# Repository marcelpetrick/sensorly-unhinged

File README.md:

<div align="center">

# sensorly-unhinged

### A tiny sensor. Two very different ways to build it.

**My very first PCB project — an open hardware experiment in measuring the cost of compactness.**

[Explore the two designs](#meet-the-contenders) · [See what is verified](#status) · [Build it yourself](#build) · [Follow the plan](plan.md)

</div>

A battery-powered indoor temperature and humidity node sounds simple. Put the
sensor next to a radio, charger and battery, though, and the board can become
part of what it measures.

This project asks a practical question: **is a larger, thermally isolated design
worth its extra space, cost and mechanical complexity?** Instead of choosing by
intuition, it develops one electrical platform in two physical forms, with a
predeclared experiment to decide between them.

**Author:** [Marcel Petrick](mailto:mail@marcelpetrick.it) · **License:** [GPL-3.0-or-later](LICENSE)

**AI disclosure:** this project is generated with AI. Its design claims still need
traceable sources, review and physical verification.

## Meet the contenders

| **A — Compact · HW A1** | **B — Thermally isolated · HW B1** |
|:---:|:---:|
|  |  |
| **30 × 34 mm** PCB | **30 × 51 mm** PCB envelope |
| One rectangle; sensor at the edge | Sensor island on a **3.5 × 8 mm** FR-4 neck |
|  |  |
| **47.0 × 39.2 × 19.6 mm** enclosure | **47.0 × 56.2 × 19.6 mm** enclosure |
| One chamber | Two chambers, divided at the neck |

*These are generated previews, not photographs. Board renders omit component
bodies; enclosure fit and thermal benefit remain unmeasured.* Dimensions come
from the [floorplan](docs/40-floorplans.md) and
[enclosure model](docs/80-enclosure.md).

Both variants share the **ESP32-C6-MINI-1**, **SHT45-AD1F**, **BQ24074** charger,
**TPS62840** regulator, schematic, BOM and firmware. A protected 1S LiPo and
USB-C provide the power interfaces. Only geometry, thermal isolation and the
enclosure change.

The experiment is **5 A + 5 B**, compared with a reference instrument. The
[thermal test plan](docs/50-thermal-ab-test-plan.md) declares the decision gate
before the boards exist — including the conditions under which the simpler
compact design wins. B has to earn its extra space.

## What makes this worth following

- **The comparison stays fair.** One shared electrical model emits both boards;
  changes to values, nets and rules are considered together.
- **The case is part of the instrument.** Vents, chamber walls, battery placement
  and sensor supports belong in the thermal design.
- **Measure first, transmit later.** The firmware contract requires acquisition
  before the radio powers up; the current bring-up image keeps the radio off.
- **The work is inspectable.** Parametric KiCad generation, OpenSCAD models,
  datasheet references, fault-injection tests and release gates live alongside
  the design. Failed experiments remain in the execution history.

## Status

> **Engineering prototype — not ready for fabrication or use.**
> Source checks pass; complete routing, supplier reviews and real-hardware
> qualification are still required.

The current routing checkpoint (2026-11-13) is recorded in [the plan](plan.md):

| Check | Current evidence |
|---|---|
| Shared electrical design | One schematic, BOM and firmware for A and B |
| ERC / DRC / schematic parity | **0 violations, 0 errors, 0 warnings, 0 parity differences** |
| Routing | **A: 18 / B: 12 open connections**; zero GND/USB-data airwires |
| Reproducibility | Generated sources regenerate byte-identically |
| Local verification | Local checkpoint `9d3ba3a`: **15 stages**, 166 host tests and 41 actual KiCad controls pass; A18/B12 opens remain |
| Bring-up firmware | Pinned ESP-IDF build; radio disabled; acquired samples written to a reviewed flash journal |
| Physical qualification | Still open; no measured A/B advantage or qualified charging claim |

Exact routing counts live in [`hardware/drc-budget.json`](hardware/drc-budget.json).
The [execution record](docs/01-execution-plan.md) retains source revisions and
verification history. BLE provisioning, MQTT/TLS delivery, signed OTA and the
remaining product behavior are tracked in the
[firmware contract](docs/71-firmware-contract.md).

**Next:** finish routing → complete independent design and supplier reviews →
produce and inspect the controlled 5 + 5 lot → run the A/B experiment → revise
and qualify a controlled 20-unit series. The [flight manual](docs/02-flight-manual.md)
provides the procedures and stop conditions.

The [first engineering source prerelease](https://github.com/marcelpetrick/sensorly-unhinged/releases/tag/engineering-2026-10-22)
is available to explore. It is a source snapshot, not a manufacturing release.
The quality badge tracks `master`; the repository-owned release labels describe
that separate release state without an empty workflow or nonexistent-latest-release badge.

## Follow the circuit

One schematic feeds both layouts. Start with the
[electrical design specification](docs/30-electrical-design-spec.md) for values,
sources and open decisions, or open the
[KiCad source](hardware/schematic/env-sensor.kicad_sch).

## Build

Everything runs from `make`. The full local gate prints a PASS/FAIL summary:

```bash
./localPipeline.sh
```

For a first look without KiCad:

```bash
make check          # shared-model rules
make test           # host regression and fault-injection tests
make firmware-test  # C sensor-decoder and flash-journal tests
```

Python-only checks include `check`, `test`, `bom`, `thermal`, `cost` and `power`.
Firmware host tests require a C compiler and standard C development headers
(`gcc` and `libc6-dev` on the Debian CI image). ERC/DRC and exports require
**KiCad 10** (`kicad-cli`); enclosure meshes require **OpenSCAD**. The real
firmware build uses pinned **ESP-IDF v5.5.4** — follow the
[bring-up instructions](docs/72-firmware-bringup.md).

<details>
<summary><strong>Build commands and release gates</strong></summary>

```bash
make license        # SPDX headers on authored source
make gen            # shared schematic, both boards, rules and model SVGs
make erc drc        # shared schematic + filled-board checks and parity
make bom            # BOM and netlist from the shared model
make thermal cost   # geometry-based screening model and cost estimate
make mech           # enclosure checks, parameters and available STL outputs
make outputs        # DRAFT Gerbers, drill, CPL, assembly PDF and STEP
make render         # board PNG previews
make mech-render    # enclosure PNG previews; graphics display required
make power          # illustrative budget; replace assumptions with measurements
make firmware       # source the pinned ESP-IDF export.sh first
make prototype-check
make prototype-package PROTOTYPE_VARIANT=a
make release-check
make release-package RELEASE_TAG=hw-a1
```

The package commands are deliberately blocked while their required evidence or
complete routing is missing. Use the selected board's printed revision and
variant when packaging; `hw-a1` and `a` above are examples.

GitHub's **Hardware Quality** workflow runs `localPipeline.sh` and retains draft
outputs for 14 days. The manual **Hardware Release** workflow checks the printed
revision, complete routing, qualification evidence and source provenance before
packaging. Publication is opt-in and draft by default. A clean development DRC
or a successful `make outputs` does not authorize an order.

Read [release packaging](docs/64-release-packaging.md) and the
[prototype-to-production handoff](docs/65-prototype-to-production.md) before
preparing either kind of package.

</details>

## Find your way around

| If you want to… | Start here |
|---|---|
| See what is next | [Current plan](plan.md) · [Verified history](docs/01-execution-plan.md) |
| Understand the circuit | [Component choices](docs/20-component-selection.md) · [Electrical specification](docs/30-electrical-design-spec.md) |
| Inspect the physical trade-off | [Floorplans](docs/40-floorplans.md) · [Thermal screening model](docs/45-thermal-model.md) · [Enclosure](docs/80-enclosure.md) |
| Examine the experiment | [Predeclared A/B test plan](docs/50-thermal-ab-test-plan.md) |
| Check sourcing and cost | [Cost estimate](docs/60-manufacturing-cost.md) · [Cost reduction](docs/61-cost-reduction.md) · [Component audit](docs/96-component-audit-20261110.md) |
| Bring up a real sample | [Power qualification](docs/51-power-safety-qualification.md) · [Firmware and capture](docs/72-firmware-bringup.md) |
| Contribute or review | [Current implementation review](docs/99-current-state-review-20261112.md) · [Working agreement](AGENTS.md) · [Flight manual](docs/02-flight-manual.md) · [Requirements](docs/10-requirements.md) |
| Explore the longer journey | [14-phase roadmap](docs/00-plan.md) · [Original vision](docs/vision.md) |

```text
tools/boardgen/  shared electrical model, geometry, placement, routing and checks
hardware/       shared schematic, A/B layouts and verified libraries
mechanical/     OpenSCAD enclosures and generated parameters
firmware/       ESP-IDF bring-up application and host tests
production/     flashing, fixture capture and factory-test tooling
measurements/   protocols and raw-data structure for physical experiments
docs/           decisions, sources, reviews and operating procedures
```

## Licence

**GPL-3.0-or-later** — see [`LICENSE`](LICENSE). That covers everything authored
here: the generator, the schematic and both boards, the enclosure model, the
documents. Every authored source file carries an SPDX header, the generated
KiCad files carry it in their title block, and `make license` fails the build if
one is missing — a licence that only exists at the repository root stops
travelling the moment a file is copied out.

Two things in the tree are not ours and keep their own terms:

| | |
|---|---|
| `hardware/lib/sensorly.pretty/*` and `hardware/lib/sensorly.kicad_sym` (except the two authored parts) | from the [official KiCad libraries](https://gitlab.com/kicad/libraries), CC-BY-SA 4.0 **with the KiCad library exception** — which explicitly permits unlimited use in your own designs without imposing licence terms on the design itself. See `hardware/lib/README.md`. |
| Datasheet figures quoted in `docs/` | the manufacturers'. Cited, not reproduced. |

The KiCad library exception is what makes this combination clean: the footprints
can sit inside a GPL project without the CC-BY-SA terms propagating to the board.

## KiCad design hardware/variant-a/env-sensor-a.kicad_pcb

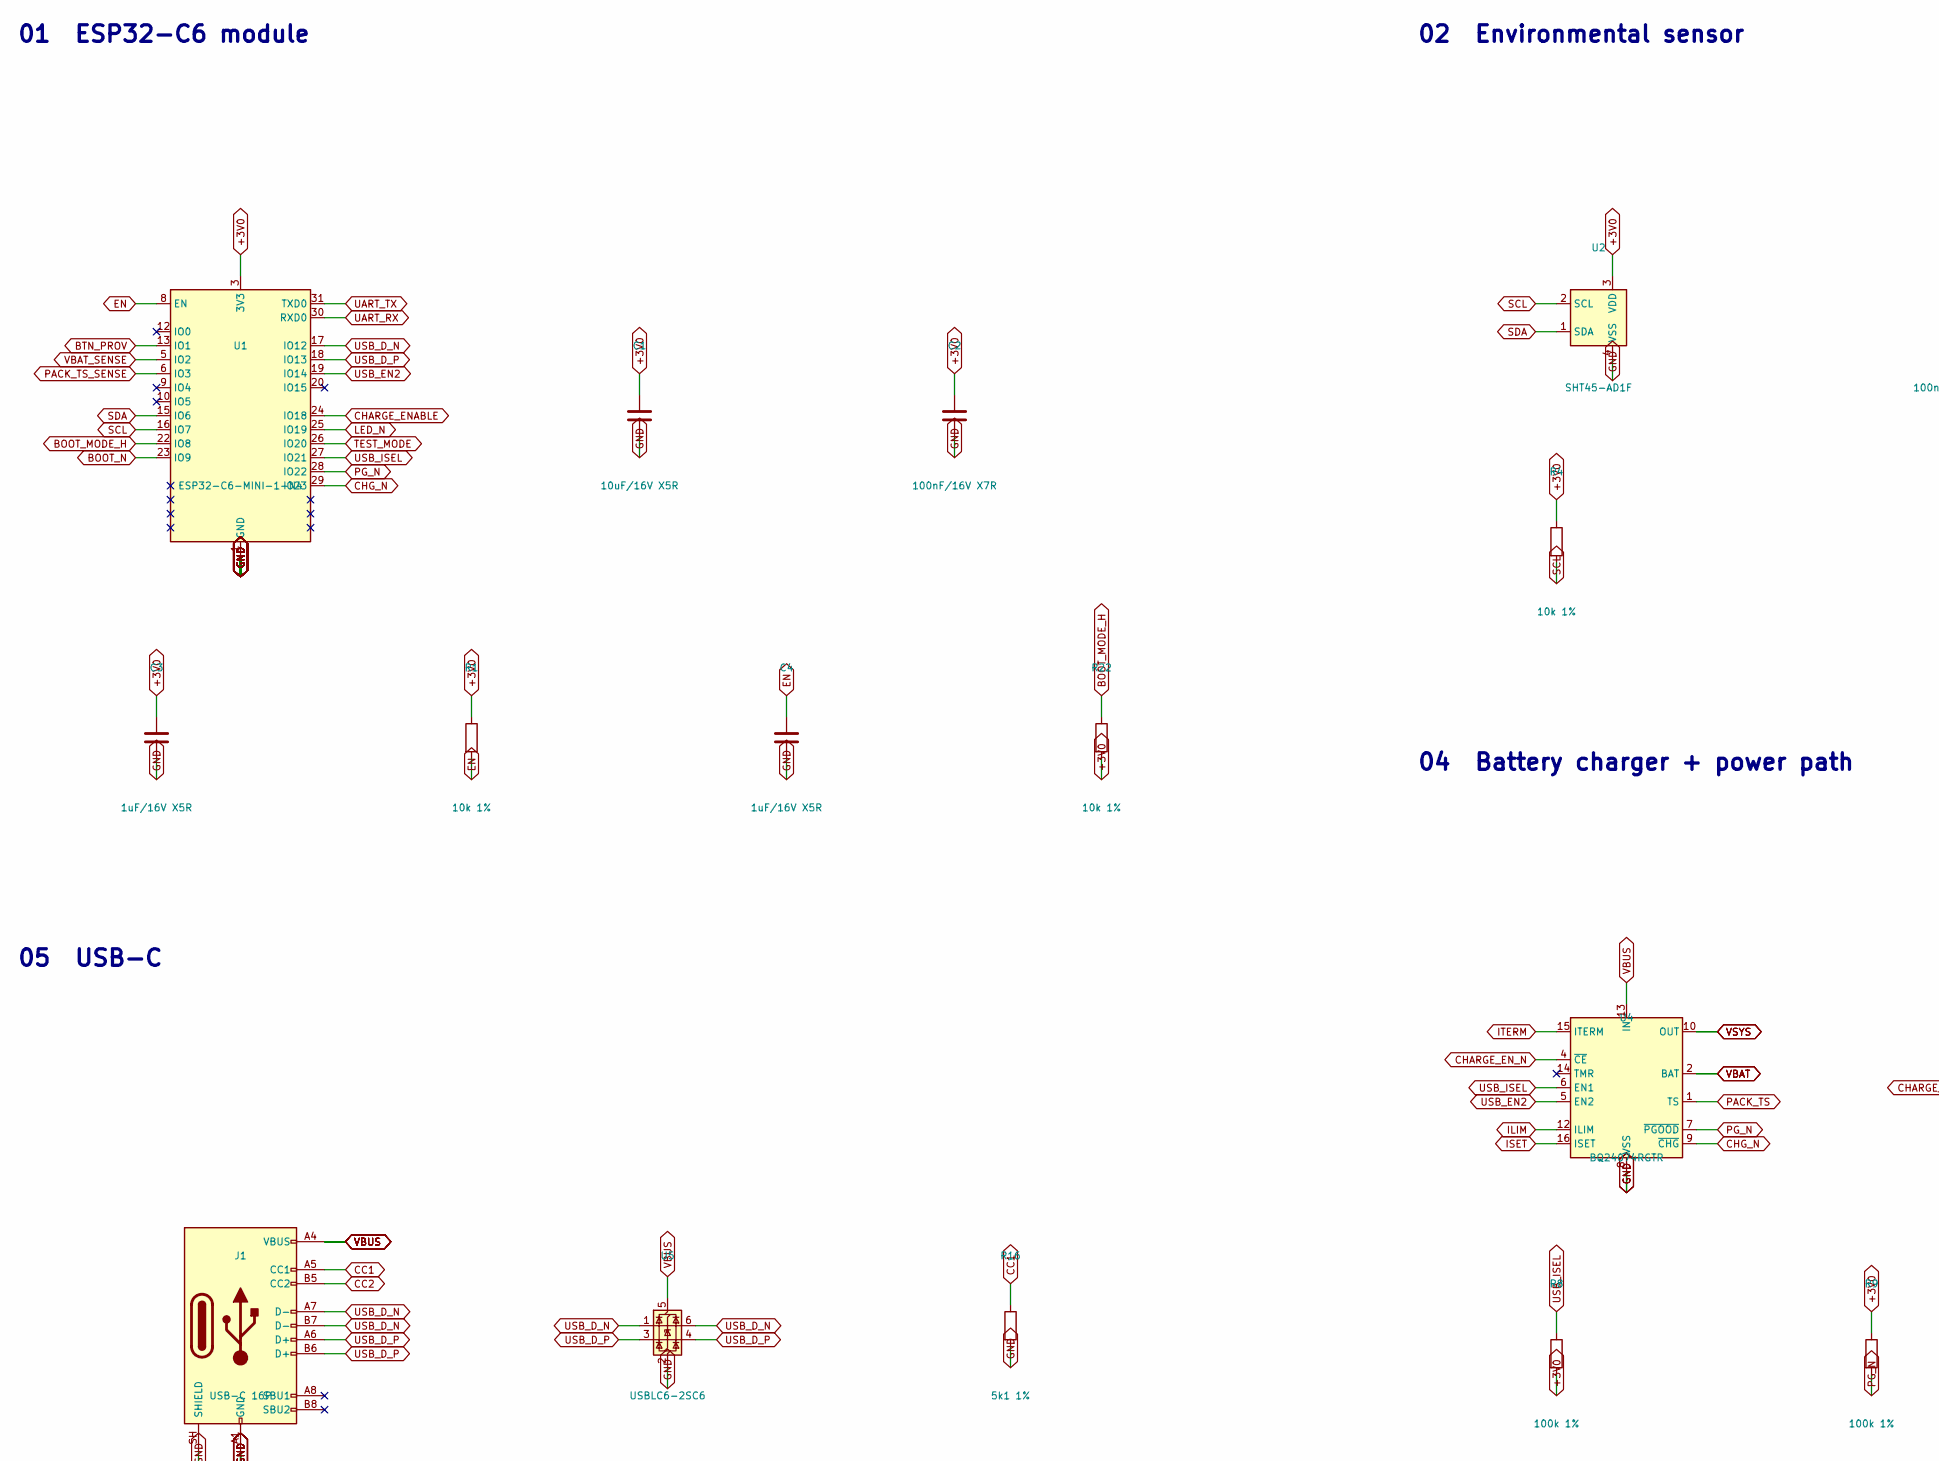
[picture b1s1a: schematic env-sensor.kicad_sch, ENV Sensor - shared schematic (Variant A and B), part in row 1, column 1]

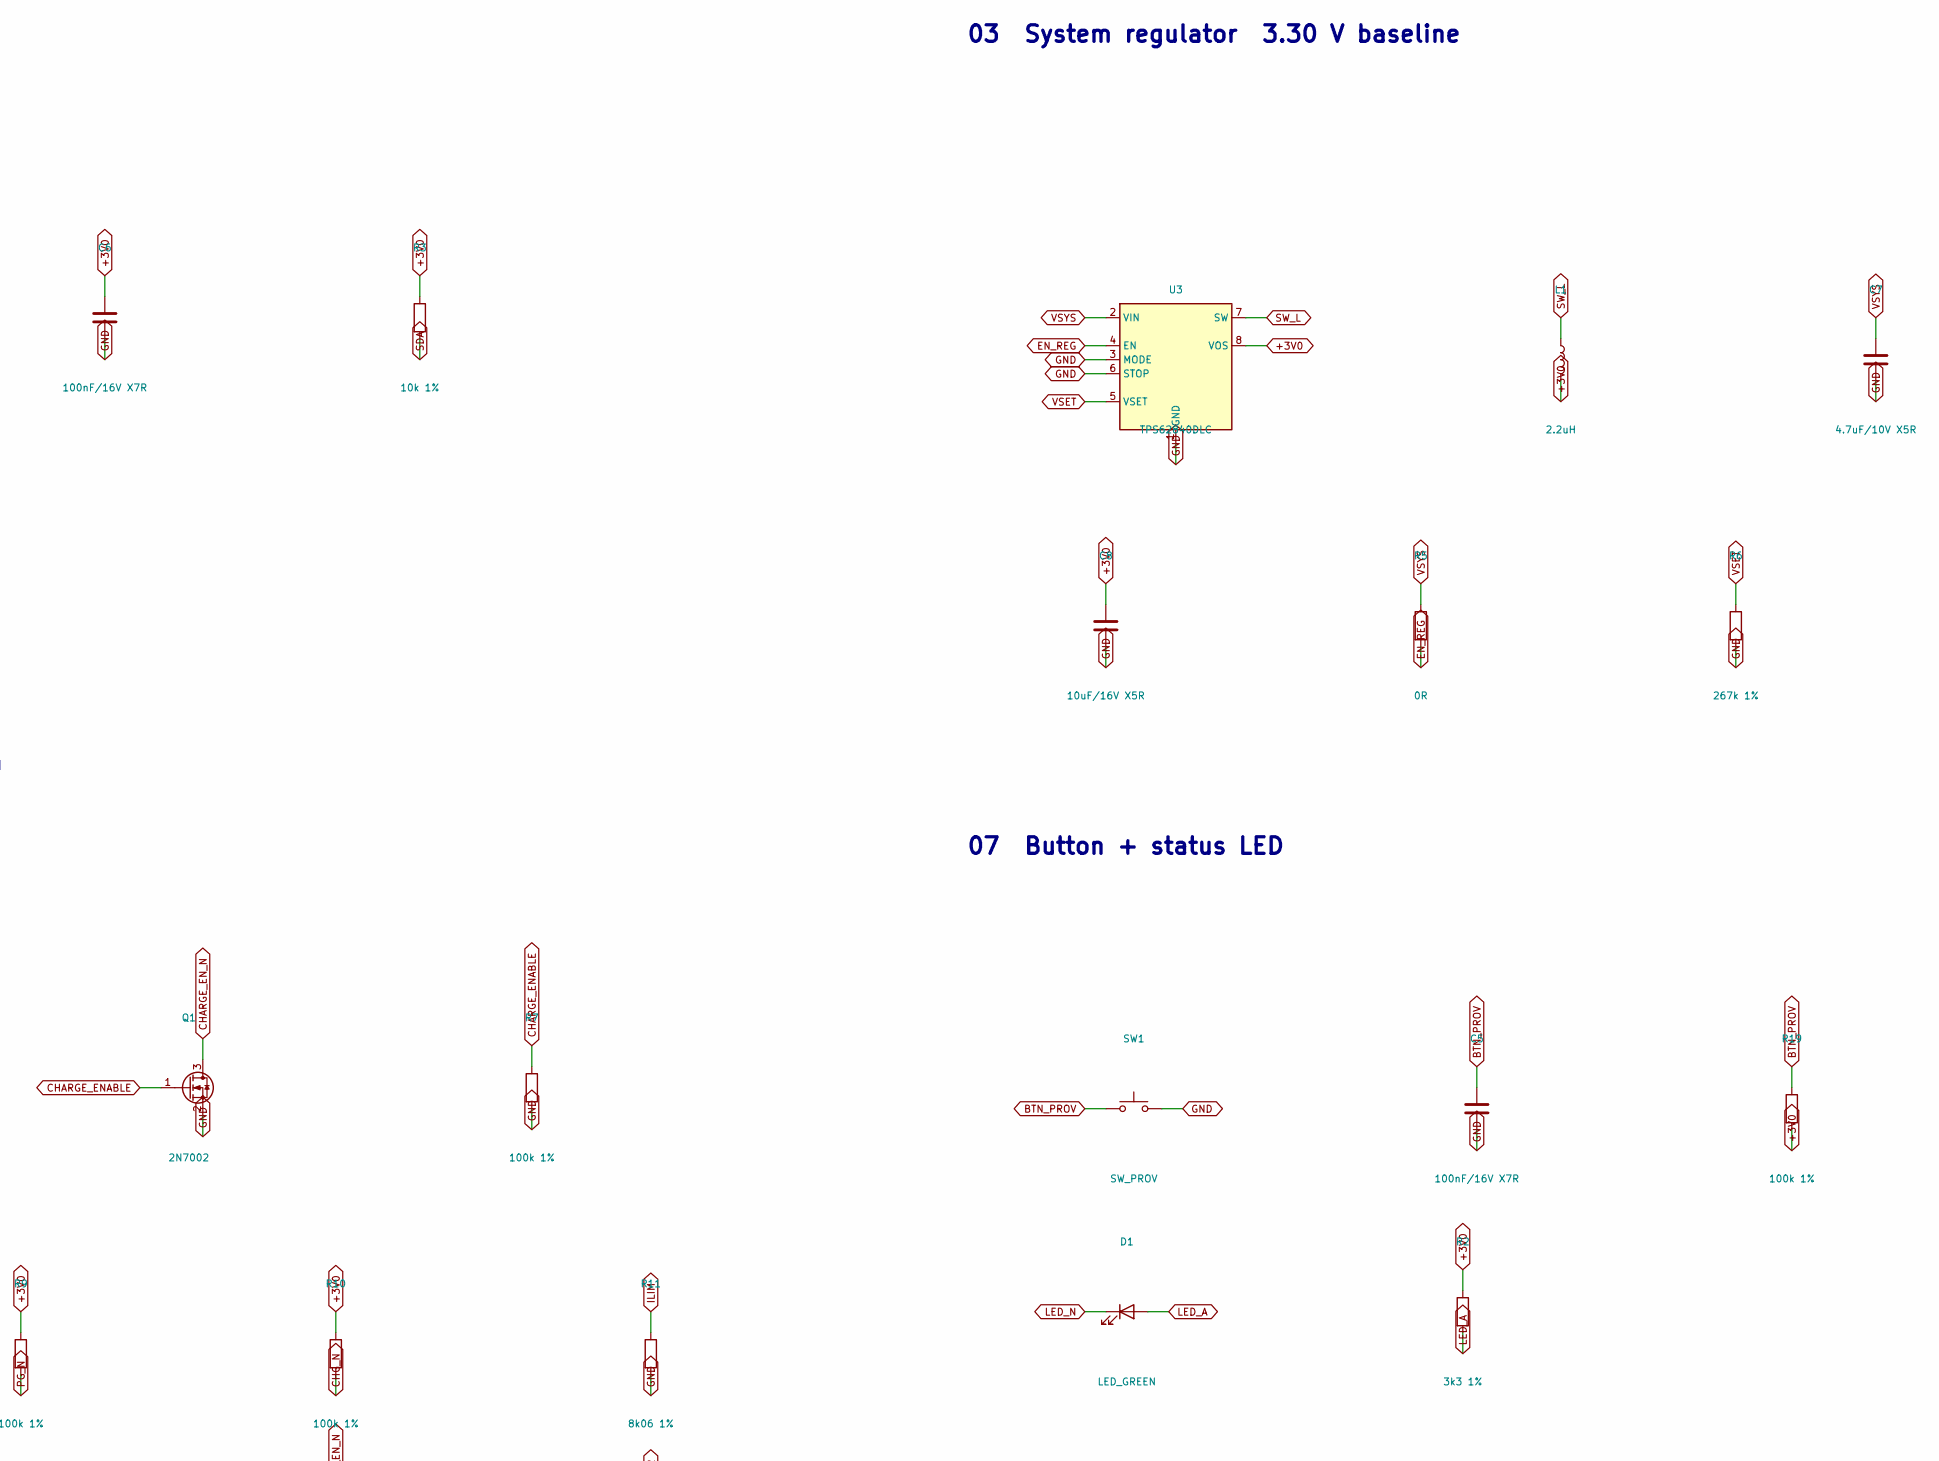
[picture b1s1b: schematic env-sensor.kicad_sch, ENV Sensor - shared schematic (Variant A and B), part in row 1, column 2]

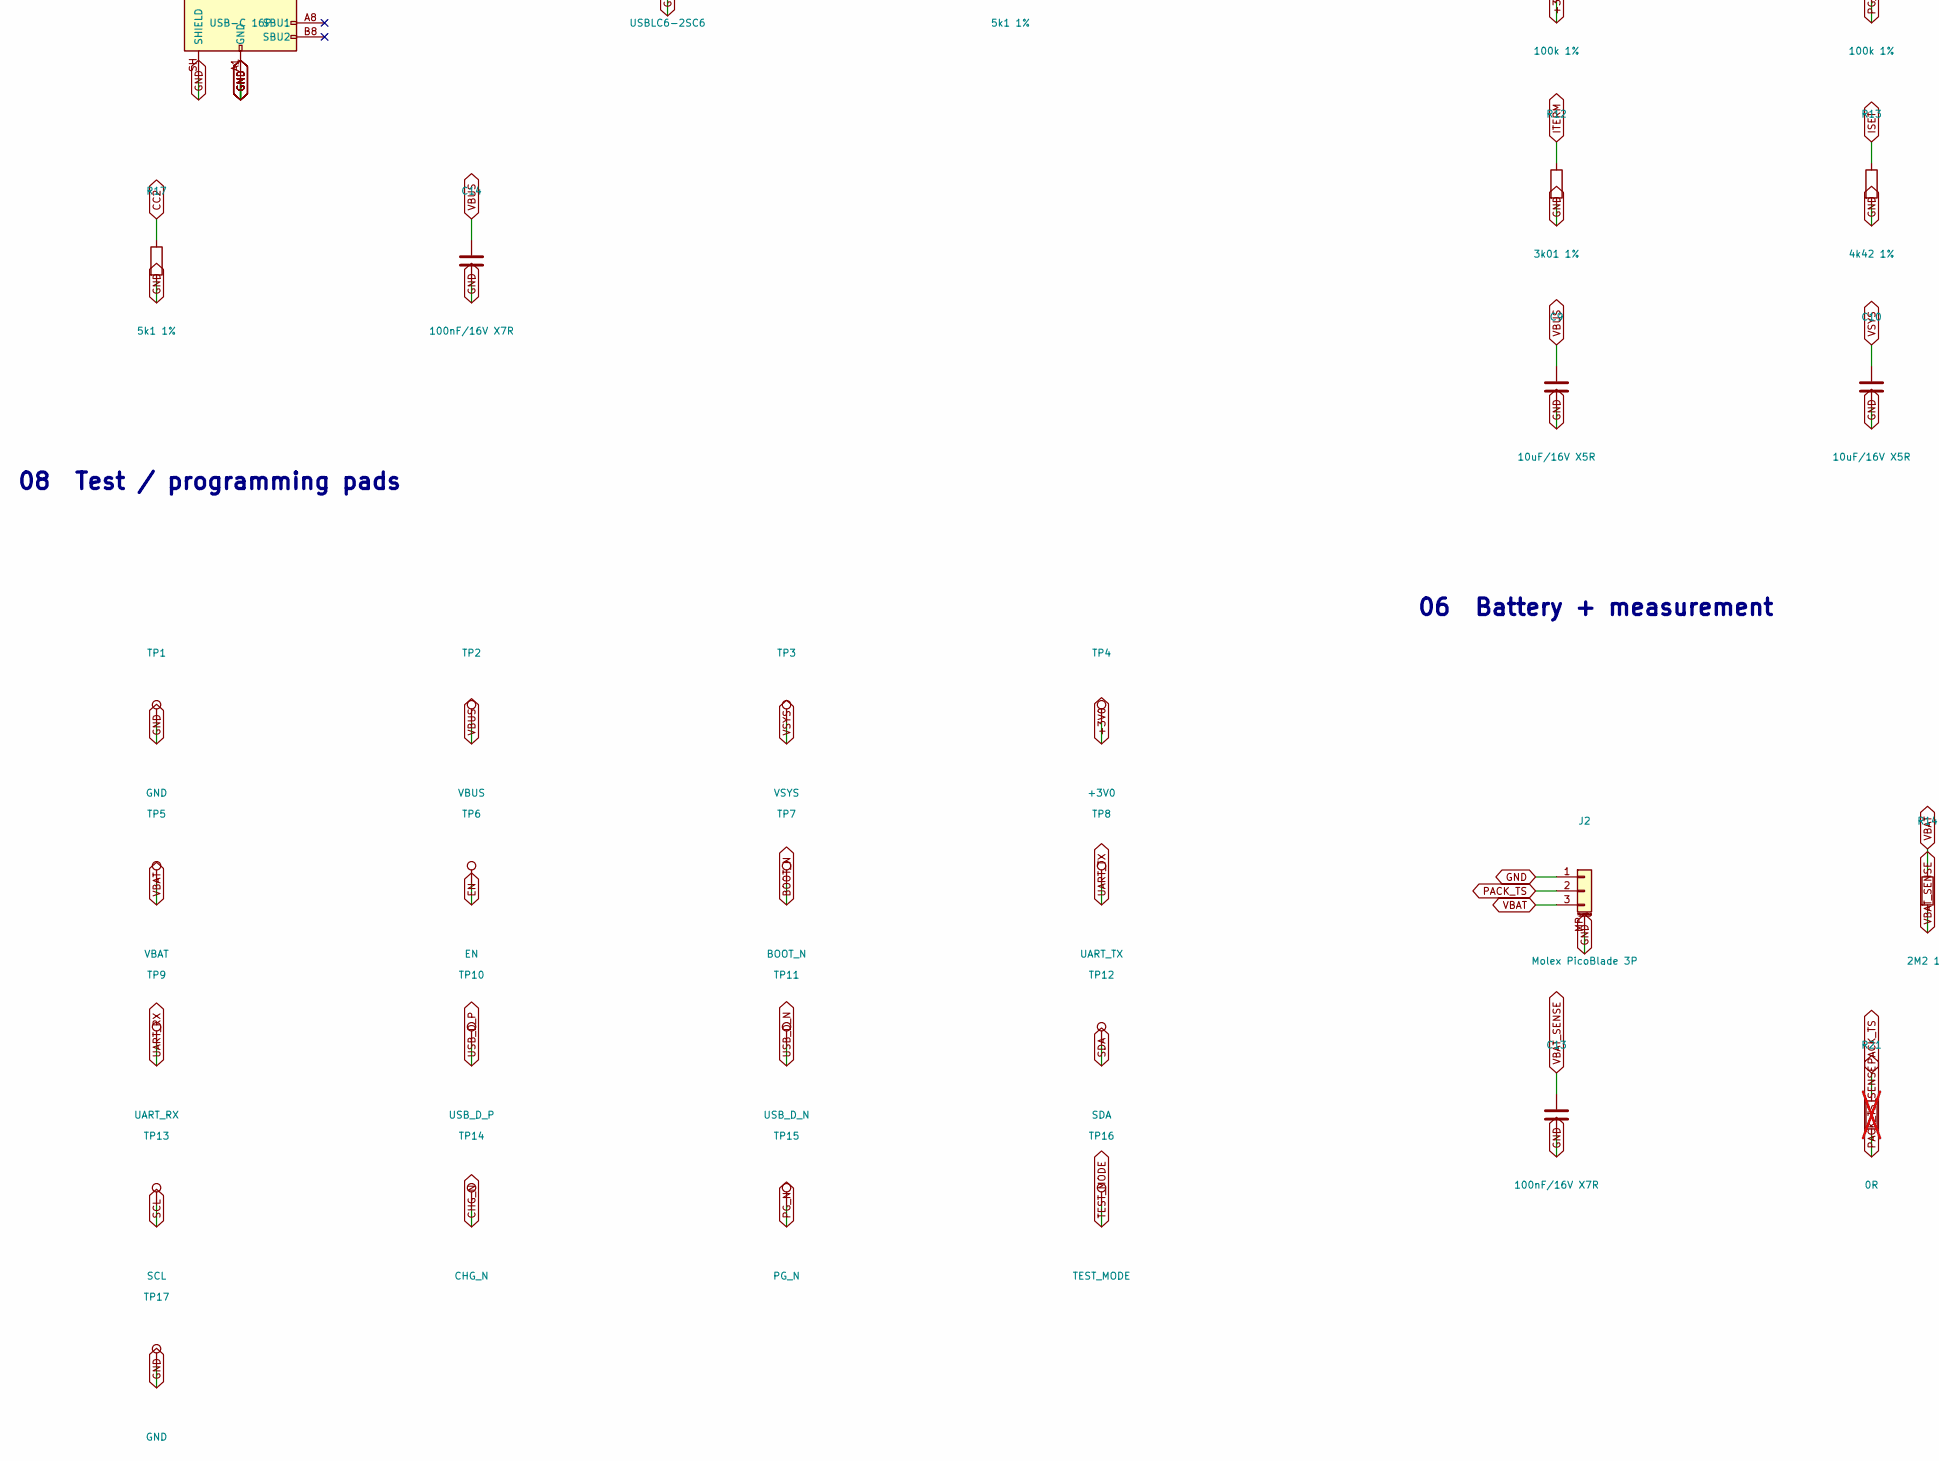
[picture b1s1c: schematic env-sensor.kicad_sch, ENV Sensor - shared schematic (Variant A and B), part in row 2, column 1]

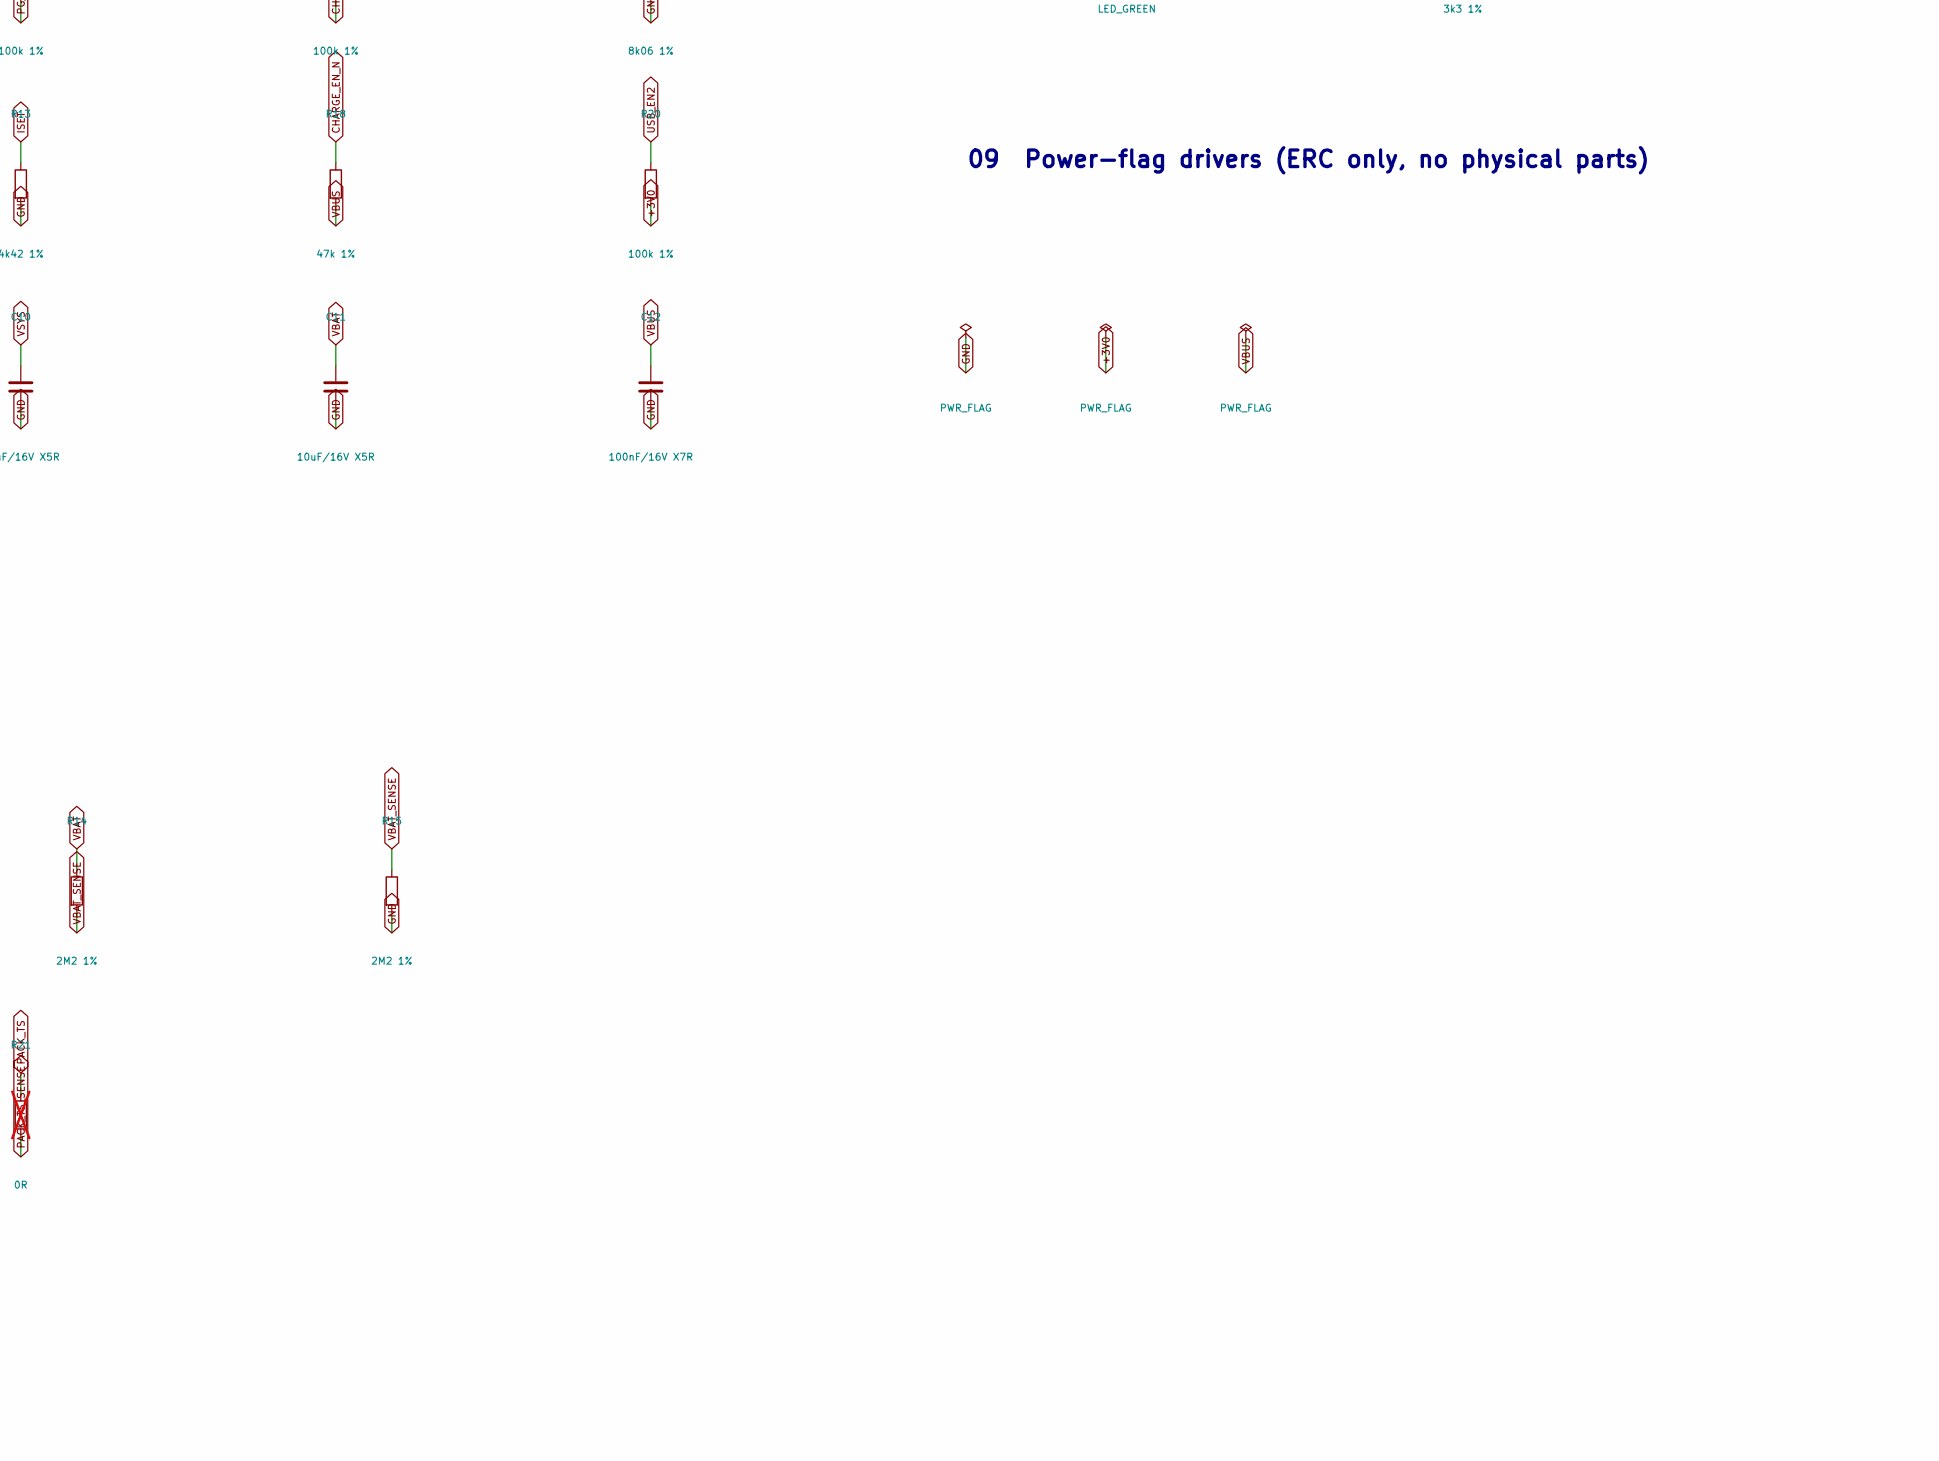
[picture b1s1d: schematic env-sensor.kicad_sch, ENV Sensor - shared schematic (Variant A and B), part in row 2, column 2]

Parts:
C1, C8, C9, C10, C11: 10uF/16V X5R; C_0805_2012Metric
C2, C5, C6, C12, C13, C14: 100nF/16V X7R; C_0402_1005Metric
C3, C4: 1uF/16V X5R; C_0402_1005Metric
C7: 4.7uF/10V X5R; C_0603_1608Metric
D1: LED_GREEN; Kingbright_KP1608SGC
J1: USB-C 16P; USB_C_Receptacle_HRO_TYPE-C-31-M-12
J2: Molex PicoBlade 3P; Molex_PicoBlade_53261-0371_1x03-1MP_P1.25mm_Horizontal
L1: 2.2uH; L_Murata_DFE201612E
Q1: 2N7002; Onsemi_CASE318_SOT23
R1, R3, R4, R22: 10k 1%; R_0402_1005Metric
R2: 3k3 1%; R_0402_1005Metric
R5: 0R; R_0402_1005Metric
R6: 267k 1%; R_0402_1005Metric
R7, R8, R9, R10, R19, R20: 100k 1%; R_0402_1005Metric
R11: 8k06 1%; R_0402_1005Metric
R12: 3k01 1%; R_0402_1005Metric
R13: 4k42 1%; R_0402_1005Metric
R14, R15: 2M2 1%; R_0402_1005Metric
R16, R17: 5k1 1%; R_0402_1005Metric
R18: 47k 1%; R_0402_1005Metric
R21: 0R; R_0402_1005Metric; not fitted
SW1: SW_PROV; Panasonic_EVQPUJ_EVQPUA
TP1, TP17: GND; TestPad_D1.5mm_Bottom
TP2: VBUS; TestPad_D1.5mm_Bottom
TP3: VSYS; TestPad_D1.5mm_Bottom
TP4: +3V0; TestPad_D1.5mm_Bottom
TP5: VBAT; TestPad_D1.5mm_Bottom
TP6: EN; TestPad_D1.5mm_Bottom
TP7: BOOT_N; TestPad_D1.5mm_Bottom
TP8: UART_TX; TestPad_D1.5mm_Bottom
TP9: UART_RX; TestPad_D1.5mm_Bottom
TP10: USB_D_P; TestPad_D1.5mm_Bottom
TP11: USB_D_N; TestPad_D1.5mm_Bottom
TP12: SDA; TestPad_D1.5mm_Bottom
TP13: SCL; TestPad_D1.5mm_Bottom
TP14: CHG_N; TestPad_D1.5mm_Bottom
TP15: PG_N; TestPad_D1.5mm_Bottom
TP16: TEST_MODE; TestPad_D1.5mm_Bottom
U1: ESP32-C6-MINI-1-N4; ESP32-C6-MINI-1
U2: SHT45-AD1F; Sensirion_DFN-4_1.5x1.5mm_P0.8mm_SHT4x_NoCentralPad
U3: TPS62840DLC; TI_DLC0008B_VSON-HR-8_2x1.5mm_P0.5mm
U4: BQ24074RGTR; TI_RGT0016B_VQFN16_3x3mm
U5: USBLC6-2SC6; ST_USBLC6_SOT23_6

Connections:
+3V0: C1.1, C2.1, C3.1, C6.1, C8.1, L1.2, R1.1, R2.1, R3.1, R4.1, R8.2, R9.1, R10.1, R19.2, R20.2, R22.2, TP4.1, U1.3 (3V3), U2.3 (VDD), U3.8 (VOS)
BOOT_MODE_H: R22.1, U1.22 (IO8)
BOOT_N: TP7.1, U1.23 (IO9)
BTN_PROV: C5.1, R19.1, SW1.1, U1.13 (IO1)
CC1: J1.A5 (CC1), R16.1
CC2: J1.B5 (CC2), R17.1
CHARGE_ENABLE: Q1.1 (G), R7.1, U1.24 (IO18)
CHARGE_EN_N: Q1.3 (D), R18.1, U4.4 (~CE)
CHG_N: R10.2, TP14.1, U1.29 (IO23), U4.9 (~CHG)
EN: C4.1, R1.2, TP6.1, U1.8 (EN)
EN_REG: R5.2, U3.4 (EN)
GND: C1.2, C2.2, C3.2, C4.2, C5.2, C6.2, C7.2, C8.2, C9.2, C10.2, C11.2, C12.2, C13.2, C14.2, J1.A1 (GND), J1.A12 (GND), J1.B1 (GND), J1.B12 (GND), J1.SH (SHIELD), J2.1, J2.MP (MountPin), Q1.2 (S), R6.2, R7.2, R11.2, R12.2, R13.2, R15.2, R16.2, R17.2, SW1.2, TP1.1, TP17.1, U1.1 (GND), U1.2 (GND), U1.11 (GND), U1.14 (GND), U1.36 (GND), U1.37 (GND), U1.38 (GND), U1.39 (GND), U1.40 (GND), U1.41 (GND), U1.42 (GND), U1.43 (GND), U1.44 (GND), U1.45 (GND), U1.46 (GND), U1.47 (GND), U1.48 (GND), U1.49 (GND), U1.50 (GND), U1.51 (GND), U1.52 (GND), U1.53 (GND), U2.4 (VSS), U3.1 (GND), U3.3 (MODE), U3.6 (STOP), U4.8 (VSS), U4.17 (VSS), U5.2 (GND)
ILIM: R11.1, U4.12 (ILIM)
ISET: R13.1, U4.16 (ISET)
ITERM: R12.1, U4.15 (ITERM)
LED_A: D1.1 (A), R2.2
LED_N: D1.2 (K), U1.25 (IO19)
PACK_TS: J2.2, R21.1, U4.1 (TS)
PACK_TS_SENSE: R21.2, U1.6 (IO3)
PG_N: R9.2, TP15.1, U1.28 (IO22), U4.7 (~PGOOD)
SCL: R4.2, TP13.1, U1.16 (IO7), U2.2 (SCL)
SDA: R3.2, TP12.1, U1.15 (IO6), U2.1 (SDA)
SW_L: L1.1, U3.7 (SW)
TEST_MODE: TP16.1, U1.26 (IO20)
UART_RX: TP9.1, U1.30 (RXD0)
UART_TX: TP8.1, U1.31 (TXD0)
USB_D_N: J1.A7 (D-), J1.B7 (D-), TP11.1, U1.17 (IO12), U5.1 (I/O1), U5.6 (I/O1)
USB_D_P: J1.A6 (D+), J1.B6 (D+), TP10.1, U1.18 (IO13), U5.3 (I/O2), U5.4 (I/O2)
USB_EN2: R20.1, U1.19 (IO14), U4.5 (EN2)
USB_ISEL: R8.1, U1.27 (IO21), U4.6 (EN1)
VBAT: C11.1, J2.3, R14.1, TP5.1, U4.2 (BAT), U4.3 (BAT)
VBAT_SENSE: C13.1, R14.2, R15.1, U1.5 (IO2)
VBUS: C9.1, C12.1, C14.1, J1.A4 (VBUS), J1.A9 (VBUS), J1.B4 (VBUS), J1.B9 (VBUS), R18.2, TP2.1, U4.13 (IN), U5.5 (VBUS)
VSET: R6.1, U3.5 (VSET)
VSYS: C7.1, C10.1, R5.1, TP3.1, U3.2 (VIN), U4.10 (OUT), U4.11 (OUT)

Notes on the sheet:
01 ESP32-C6 module
05 USB-C
08 Test / programming pads
02 Environmental sensor
04 Battery charger + power path
06 Battery + measurement
03 System regulator 3.30 V baseline
07 Button + status LED
09 Power-flag drivers (ERC only, no physical parts)

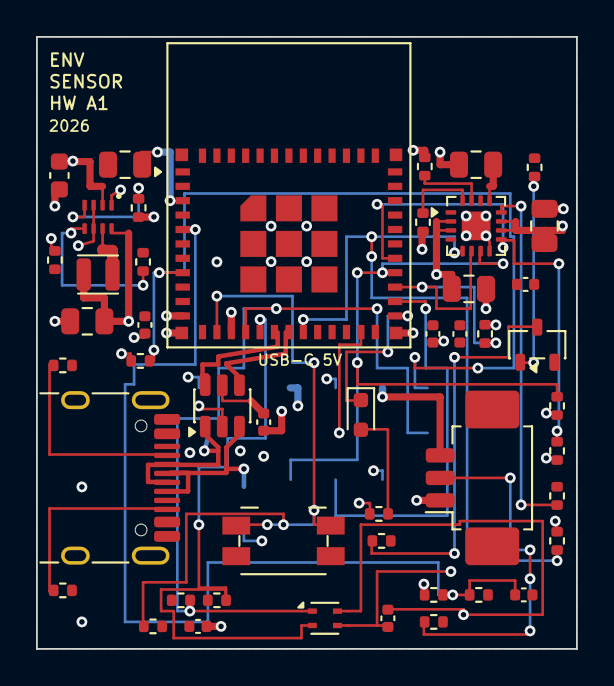
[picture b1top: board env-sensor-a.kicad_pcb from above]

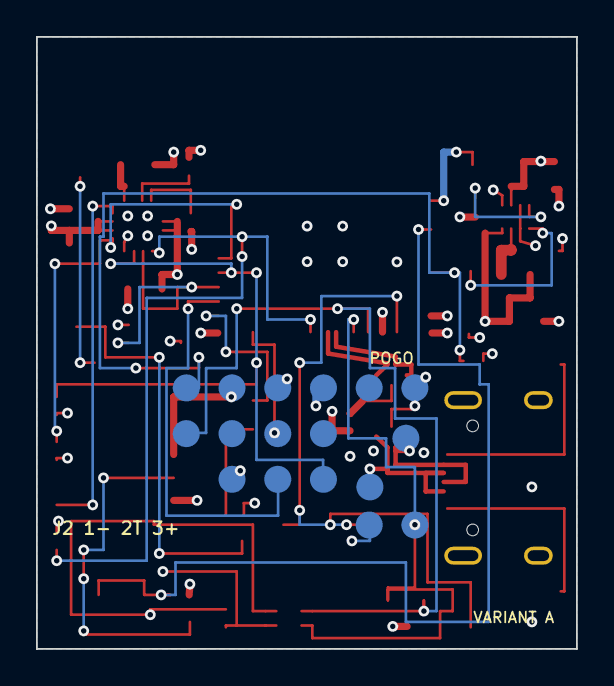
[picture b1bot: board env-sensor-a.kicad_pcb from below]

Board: 4 copper layers, 30.0 x 34.0 mm, 64 parts (17 on the bottom side), 35 nets.

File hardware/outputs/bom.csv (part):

Qty,Populate,Refs,Value,Footprint,MPN,Manufacturer,Second source,Sourcing status,Notes
1,yes,C1,10uF/16V X5R,C_0805_2012Metric,GRM21BR61C106KE15L,Murata,"single-sourced, accepted design risk; assembly qualification pending","single-sourced, accepted risk for design exploration only; alternate is unqualified, do not substitute","ESP32 entrance bulk: nominal 10uF per Espressif; total COUT upper margin, docs/63"
1,yes,C2,100nF/16V X7R,C_0402_1005Metric,GRM155R71C104KA88D,Murata,"single-sourced, accepted design risk; assembly qualification pending","single-sourced, accepted risk for design exploration only; alternate is unqualified, do not substitute",ESP32 HF decoupling
1,yes,C3,1uF/16V X5R,C_0402_1005Metric,GRM155R61C105KA12D,Murata,"single-sourced, accepted design risk; assembly qualification pending","single-sourced, accepted risk for design exploration only; alternate is unqualified, do not substitute",ESP32 mid-frequency decoupling
1,yes,C4,1uF/16V X5R,C_0402_1005Metric,GRM155R61C105KA12D,Murata,"single-sourced, accepted design risk; assembly qualification pending","single-sourced, accepted risk for design exploration only; alternate is unqualified, do not substitute",EN RC delay (~10 ms)
1,yes,C5,100nF/16V X7R,C_0402_1005Metric,GRM155R71C104KA88D,Murata,"single-sourced, accepted design risk; assembly qualification pending","single-sourced, accepted risk for design exploration only; alternate is unqualified, do not substitute",SW1 debounce
1,yes,C6,100nF/16V X7R,C_0402_1005Metric,GRM155R71C104KA88D,Murata,"single-sourced, accepted design risk; assembly qualification pending","single-sourced, accepted risk for design exploration only; alternate is unqualified, do not substitute",sensor VDD decoupling - ONLY passive on the island
1,yes,C7,4.7uF/10V X5R,C_0603_1608Metric,GRM188R61A475KE15D,Murata,"single-sourced, accepted design risk; assembly qualification pending","single-sourced, accepted risk for design exploration only; alternate is unqualified, do not substitute",buck input - 4.7 uF required at VIN
1,yes,C8,10uF/16V X5R,C_0805_2012Metric,GRM21BR61C106KE15L,Murata,"single-sourced, accepted design risk; assembly qualification pending","single-sourced, accepted risk for design exploration only; alternate is unqualified, do not substitute","buck output; stronger DC-bias margin, GRM21BR61C106KE15L, docs/63"
1,yes,C9,10uF/16V X5R,C_0805_2012Metric,GRM21BR61C106KE15L,Murata,"single-sourced, accepted design risk; assembly qualification pending","single-sourced, accepted risk for design exploration only; alternate is unqualified, do not substitute",charger IN bypass
1,yes,C10,10uF/16V X5R,C_0805_2012Metric,GRM21BR61C106KE15L,Murata,"single-sourced, accepted design risk; assembly qualification pending","single-sourced, accepted risk for design exploration only; alternate is unqualified, do not substitute",charger OUT bypass
1,yes,C11,10uF/16V X5R,C_0805_2012Metric,GRM21BR61C106KE15L,Murata,"single-sourced, accepted design risk; assembly qualification pending","single-sourced, accepted risk for design exploration only; alternate is unqualified, do not substitute",charger BAT bypass
1,yes,C12,100nF/16V X7R,C_0402_1005Metric,GRM155R71C104KA88D,Murata,"single-sourced, accepted design risk; assembly qualification pending","single-sourced, accepted risk for design exploration only; alternate is unqualified, do not substitute",charger IN HF bypass
1,yes,C14,100nF/16V X7R,C_0402_1005Metric,GRM155R71C104KA88D,Murata,"single-sourced, accepted design risk; assembly qualification pending","single-sourced, accepted risk for design exploration only; alternate is unqualified, do not substitute",VBUS local
1,yes,C13,100nF/16V X7R,C_0402_1005Metric,GRM155R71C104KA88D,Murata,"single-sourced, accepted design risk; assembly qualification pending","single-sourced, accepted risk for design exploration only; alternate is unqualified, do not substitute",ADC filter
1,yes,D1,LED_GREEN,Kingbright_KP1608SGC,KP-1608SGC,Kingbright,"any 0603 green LED, Vf < 2.4 V at 0.5 mA","single-sourced, accepted risk for design exploration only; alternate is unqualified, do not substitute","status LED, active low"
1,yes,J1,USB-C 16P,USB_C_Receptacle_HRO_TYPE-C-31-M-12,TYPE-C-31-M-12,HRO,GCT USB4085 (different land pattern - do not swap without relayout),"single-sourced, accepted risk for design exploration only; alternate is unqualified, do not substitute","USB-C receptacle, sink only, TH mounting lugs"
1,yes,J2,Molex PicoBlade 3P,Molex_PicoBlade_53261-0371_1x03-1MP_P1.25mm_Horizontal,53261-0371,Molex,single-sourced connector family; accepted for prototypes pending pack qualification,"single-sourced, accepted risk for design exploration only; alternate is unqualified, do not substitute","LP702040 pack: pin 1 GND(-), pin 2 PACK_TS/103AT-2, pin 3 VBAT(+)"
1,yes,L1,2.2uH,L_Murata_DFE201612E,DFE201612E-2R2M=P2,Murata,"DFE201210S-2R2M (2.0x1.2 body, different land pattern; unqualified redesign candidate)","single-sourced, accepted risk for design exploration only; alternate is unqualified, do not substitute","2.2 uH, DCR 116 mOhm - datasheet SLVSEC6D Table 4"
1,yes,Q1,2N7002,Onsemi_CASE318_SOT23,2N7002LT1G,onsemi,"2N7002,215 (Nexperia; same G-S-D pinout and SOT-23 land pattern)","single-sourced, accepted risk for design exploration only; alternate is unqualified, do not substitute",low-side /CE driver; VBUS pull-up keeps charging disabled at power-up
1,yes,R1,10k 1%,R_0402_1005Metric,ERJ2RKF1002X,Panasonic,"single-sourced, accepted design risk; assembly qualification pending","single-sourced, accepted risk for design exploration only; alternate is unqualified, do not substitute",EN pull-up
1,yes,R2,3k3 1%,R_0402_1005Metric,ERJ2RKF3301X,Panasonic,"single-sourced, accepted design risk; assembly qualification pending","single-sourced, accepted risk for design exploration only; alternate is unqualified, do not substitute","LED series, ~0.5 mA"
1,yes,R3,10k 1%,R_0402_1005Metric,ERJ2RKF1002X,Panasonic,"single-sourced, accepted design risk; assembly qualification pending","single-sourced, accepted risk for design exploration only; alternate is unqualified, do not substitute","SDA pull-up - main board, never on the island"
1,yes,R4,10k 1%,R_0402_1005Metric,ERJ2RKF1002X,Panasonic,"single-sourced, accepted design risk; assembly qualification pending","single-sourced, accepted risk for design exploration only; alternate is unqualified, do not substitute","SCL pull-up - main board, never on the island"
1,yes,R5,0R,R_0402_1005Metric,ERJ2GE0R00X,Panasonic,"single-sourced, accepted design risk; assembly qualification pending","single-sourced, accepted risk for design exploration only; alternate is unqualified, do not substitute",EN tie - a resistor so EN can be lifted to measure Iq
1,yes,R6,267k 1%,R_0402_1005Metric,ERJ2RKF2673X,Panasonic,"single-sourced, accepted design risk; assembly qualification pending","single-sourced, accepted risk for design exploration only; alternate is unqualified, do not substitute",VSET -> 3.30 V. Characterization only: 52k3 -> 3.00 V
1,yes,R7,100k 1%,R_0402_1005Metric,ERJ2RKF1003X,Panasonic,"single-sourced, accepted design risk; assembly qualification pending","single-sourced, accepted risk for design exploration only; alternate is unqualified, do not substitute",Q1 gate pull-down: charge enable defaults low/off
1,yes,R8,100k 1%,R_0402_1005Metric,ERJ2RKF1003X,Panasonic,"single-sourced, accepted design risk; assembly qualification pending","single-sourced, accepted risk for design exploration only; alternate is unqualified, do not substitute","EN1 pull-up to MCU rail: with EN2 high selects standby, ADR-001"
1,yes,R9,100k 1%,R_0402_1005Metric,ERJ2RKF1003X,Panasonic,"single-sourced, accepted design risk; assembly qualification pending","single-sourced, accepted risk for design exploration only; alternate is unqualified, do not substitute",/PGOOD pull-up
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

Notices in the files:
README.md:
License: GPL v3 or later
hardware/schematic/env-sensor.kicad_sch:
SPDX-FileCopyrightText: 2026 Marcel Petrick
SPDX-License-Identifier: GPL-3.0-or-later
